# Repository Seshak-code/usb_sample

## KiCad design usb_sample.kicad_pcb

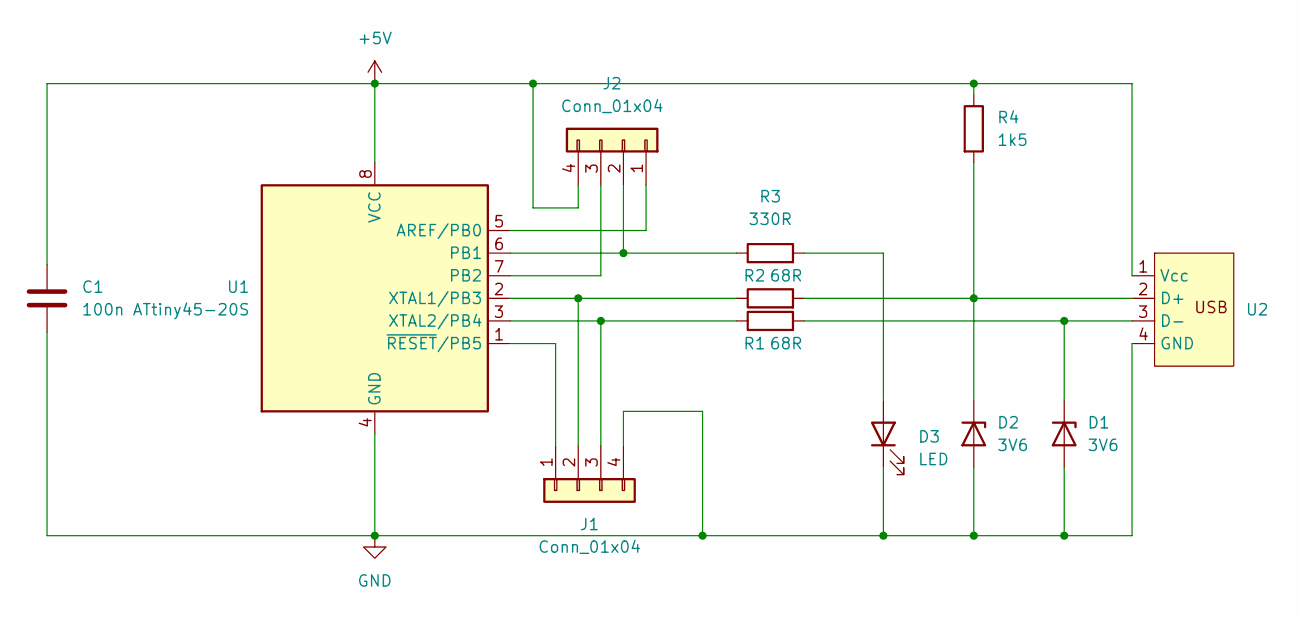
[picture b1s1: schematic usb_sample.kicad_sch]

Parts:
C1: 100n; C_1206_3216Metric_Pad1.33x1.80mm_HandSolder
D1, D2: 3V6; D_SOD-123
D3: LED; LED_D3.0mm
J1, J2: Conn_01x04; PinHeader_1x04_P2.54mm_Vertical
R1, R2: 68R; R_0805_2012Metric_Pad1.20x1.40mm_HandSolder
R3: 330R; R_0805_2012Metric_Pad1.20x1.40mm_HandSolder
R4: 1k5; R_0805_2012Metric_Pad1.20x1.40mm_HandSolder
U1: ATtiny45-20S; SOIC-8_5.3x5.3mm_P1.27mm
U2: PCB_USB_connector

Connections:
+5V: C1.1, J2.4, R4.1, U1.8 (VCC), U2.1 (Vcc)
GND: C1.2, D1.2 (A), D2.2 (A), D3.1 (K), J1.4, U1.4 (GND), U2.4 (GND)
unnamed: D1.1 (K), R1.2, U2.3 (D-)
unnamed: D2.1 (K), R2.2, R4.2, U2.2 (D+)
unnamed: D3.2 (A), R3.2
unnamed: J1.1, U1.1 (~RESET/PB5)
unnamed: J1.2, R2.1, U1.2 (XTAL1/PB3)
unnamed: J1.3, R1.1, U1.3 (XTAL2/PB4)
unnamed: J2.1, U1.5 (AREF/PB0)
unnamed: J2.2, R3.1, U1.6 (PB1)
unnamed: J2.3, U1.7 (PB2)

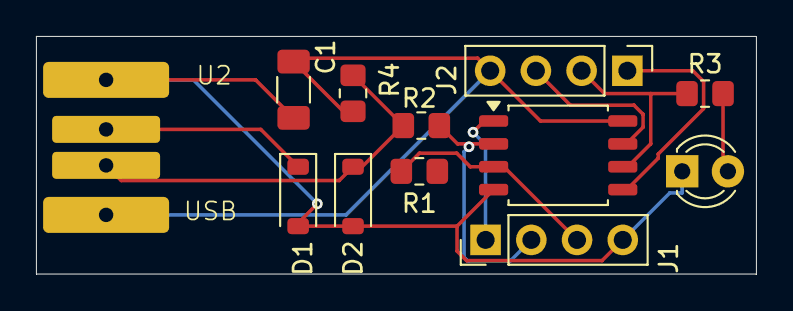
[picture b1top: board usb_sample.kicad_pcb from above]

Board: 2 copper layers, 40.0 x 13.2 mm, 12 parts (0 on the bottom side), 11 nets.

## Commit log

2026-05-25 chore: add .gitignore to exclude user history and system files
2026-05-25 Remove .gitignore from repository tracking
2026-05-25 Remove KiCad backups, lock files, and macOS/Git artifacts from tracking
